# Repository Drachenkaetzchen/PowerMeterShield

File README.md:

#### **Voltage and Current Meter Shield**

This is a shield to measure voltage (±30V) and current (±10A). It is isolated, so you can hook it up either polarity and even measure negative voltages.

#### **Usage Ideas**
- Combine this shield with an SD card shield to create a data-logging multimeter.
- Combine this shield with a WiFi-Shield to log data to the internet.
- Use the WiFi shield with a solar panel to measure how much power you harvest
- Measure the power consumption of your QuadCopter during flight

#### **Theory of Operation**

Voltage is measured using the THS4521 differential amplifier by converting a bipolar single-ended voltage into a differential voltage, which is fed into the ADC.

Current is measured via the 5mΩ shunt resistor and amplified using the INA170 high-side current shunt monitor. It is converted into a voltage and fed into the ADC.  A 1.024V reference is used to level shift the signal for the ADC so that we can measure negative currents as well (negative range: 0-1.024V and positive range 1.024V to 2.048V).

The ADC used is a MCP3426, which supports up to 16 bits of resolution and an integrated gain amplifier (1x, 2x, 4x and 8x), so if you don't need the full input range of ±30V, you can measure smaller voltages with higher resolutions. The ADC is controlled via I²C.

The ADUM1250 isolates the I²C communications and a 5V DC to DC converter isolates the power rails for the shield.

#### **Specifications**
- Voltage Measurements from -30V to +30V
- Current Measurement from -10A to +10A
- Resolution is 12, 14 or 16 bits. This affects the sample rate (Samples per Second or SPS). 15 SPS at 16 Bits, 60 SPS at 14 Bits and 240 SPS at 12 Bits.
- Digital Gain control of 1x, 2x, 4x or 8x gain
- Input Impedance: >10MΩ
- Burden Voltage: 5mV/A
- Resolution for Voltage Measurements at 16 bit: 4mV at 1x gain (±30V), 2mV at 2x gain (±15V), 1mV at 4x gain (±7.5V) and 0.5mV at 8x gain (±3.75V)
- Resolution for Current Measurements at 16 bit: 1.2mA at 1x gain (±10A), 0.6mA at 2x gain (±5A), 0.3mA at 4x gain (±2.5A) and 0.15mA at 8x gain (±1.25A)
- Works out of the box with all Arduino platforms that feature VREF, SDA and SCL pins. For older Arduino platforms, you may wire VREF to +5V and SDA/SCL to A4/A5 pins.

#### **Project History**

I have built a [solar powered router](http://felicitus.org/solarwind/) for which I have designed a voltage and current measurement board. The voltage and current meter shield evolved from that monitoring board.

I have taken great care to make this shield relatively safe; it doesn't matter which way you connect the measurement inputs - your Arduino will survive due to the isolation (unless you exceed the specified ±30V ±10A input ranges).

#### **License**

This board is licensed under the CERN OHL v1.2.

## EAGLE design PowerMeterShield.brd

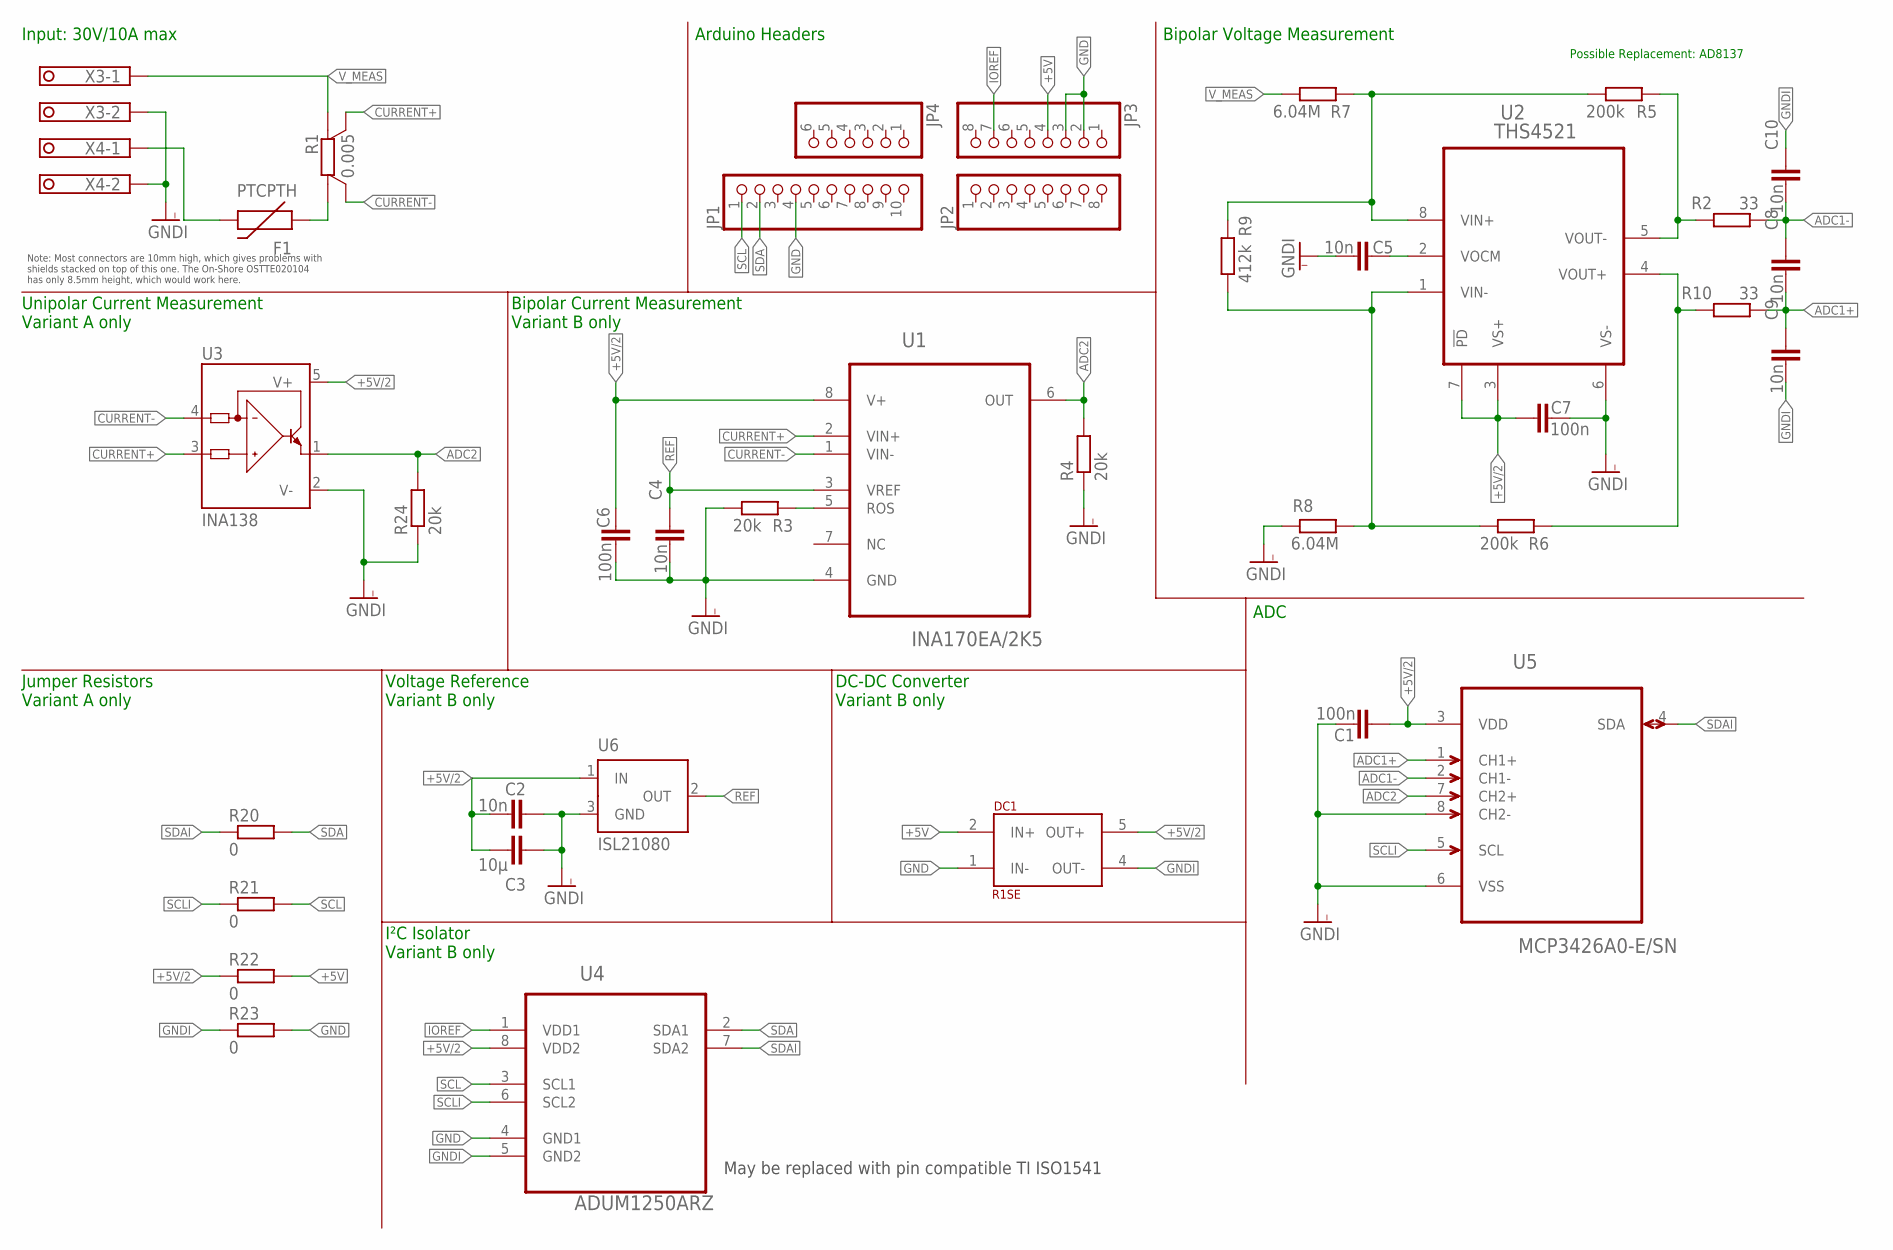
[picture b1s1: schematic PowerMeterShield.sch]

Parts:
C1, C6, C7: 100n; C0805
C2, C4, C5, C8, C9, C10: 10n; C0805
C3: 10µ; C0805
DC1: R1SE
F1: PTCPTH; PTC
JP1: PINHD-1X10; 1X10
JP2, JP3: PINHD-1X8; 1X08
JP4: PINHD-1X6; 1X06
R1: 0.005; CSM3637M
R2, R10: 33; R0805
R3, R4, R24: 20k; R0805
R5, R6: 200k; R0805
R7, R8: 6.04M; R0805
R9: 412k; R0805
R20, R21, R22, R23: 0; R2010
U1: INA170EA/2K5; SOP65P490X110-8N
U2: THS4521; SOIC127P600X175-8N
U3: INA138; SOT23-5
U4: ADUM1250ARZ; SOIC127P600X175-8N
U5: MCP3426A0-E/SN; SOIC127P600X175-8N
U6: ISL21080; SOT23
X3, X4: 1751248

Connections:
+5V: DC1.2 (IN+), JP3.4, R22.2
+5V/2: C1.1, C2.1, C3.1, C6.1, C7.1, DC1.5 (OUT+), R22.1, U1.8 (V+), U2.3 (VS+), U2.7 (!PD), U3.5 (V+), U4.8 (VDD2), U5.3 (VDD), U6.1 (IN)
ADC1+: C8.1, C9.2, R10.1, U5.1 (CH1+)
ADC1+_OLD: R6.2, R10.2, U2.4 (VOUT+)
ADC1-: C8.2, C10.1, R2.1, U5.2 (CH1-)
ADC1-_OLD: R2.2, R5.2, U2.5 (VOUT-)
ADC2: R4.2, R24.2, U1.6 (OUT), U3.1 (OUT), U5.7 (CH2+)
CURRENT+: R1.S2, U1.2 (VIN+), U3.3 (IN+)
CURRENT-: R1.S1, U1.1 (VIN-), U3.4 (IN-)
GND: DC1.1 (IN-), JP1.4, JP3.2, JP3.3, R23.2, U4.4 (GND1)
GNDI: C1.2, C2.2, C3.2, C4.1, C5.1, C6.2, C7.2, C9.1, C10.2, DC1.4 (OUT-), R3.1, R4.1, R8.1, R23.1, R24.1, U1.4 (GND), U2.6 (VS-), U3.2 (V-), U4.5 (GND2), U5.6 (VSS), U5.8 (CH2-), U6.3 (GND), X3.2, X4.2
IOREF: JP3.7, U4.1 (VDD1)
unnamed: C5.2, U2.2 (VOCM)
unnamed: R5.1, R7.2, R9.2, U2.8 (VIN+)
unnamed: F1.P$1 (1), R1.I1
unnamed: R3.2, U1.5 (ROS)
unnamed: R6.1, R8.2, R9.1, U2.1 (VIN-)
REF: C4.2, U1.3 (VREF), U6.2 (OUT)
SCL: JP1.1, R21.2, U4.3 (SCL1)
SCLI: R21.1, U4.6 (SCL2), U5.5 (SCL)
SDA: JP1.2, R20.2, U4.2 (SDA1)
SDAI: R20.1, U4.7 (SDA2), U5.4 (SDA)
VIN_MEAS: F1.P$2 (2), X4.1
V_MEAS: R1.I2, R7.1, X3.1

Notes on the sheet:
Input: 30V/10A max
Voltage Reference Variant B only
DC-DC Converter Variant B only
Arduino Headers
ADC
I²C Isolator Variant B only
Bipolar Voltage Measurement
Bipolar Current Measurement Variant B only
Unipolar Current Measurement Variant A only
Jumper Resistors Variant A only
Note: Most connectors are 10mm high, which gives problems with shields stacked on top of this one. The On-Shore OSTTE020104 has only 8.5mm height, which would work here.
May be replaced with pin compatible TI ISO1541
Possible Replacement: AD8137

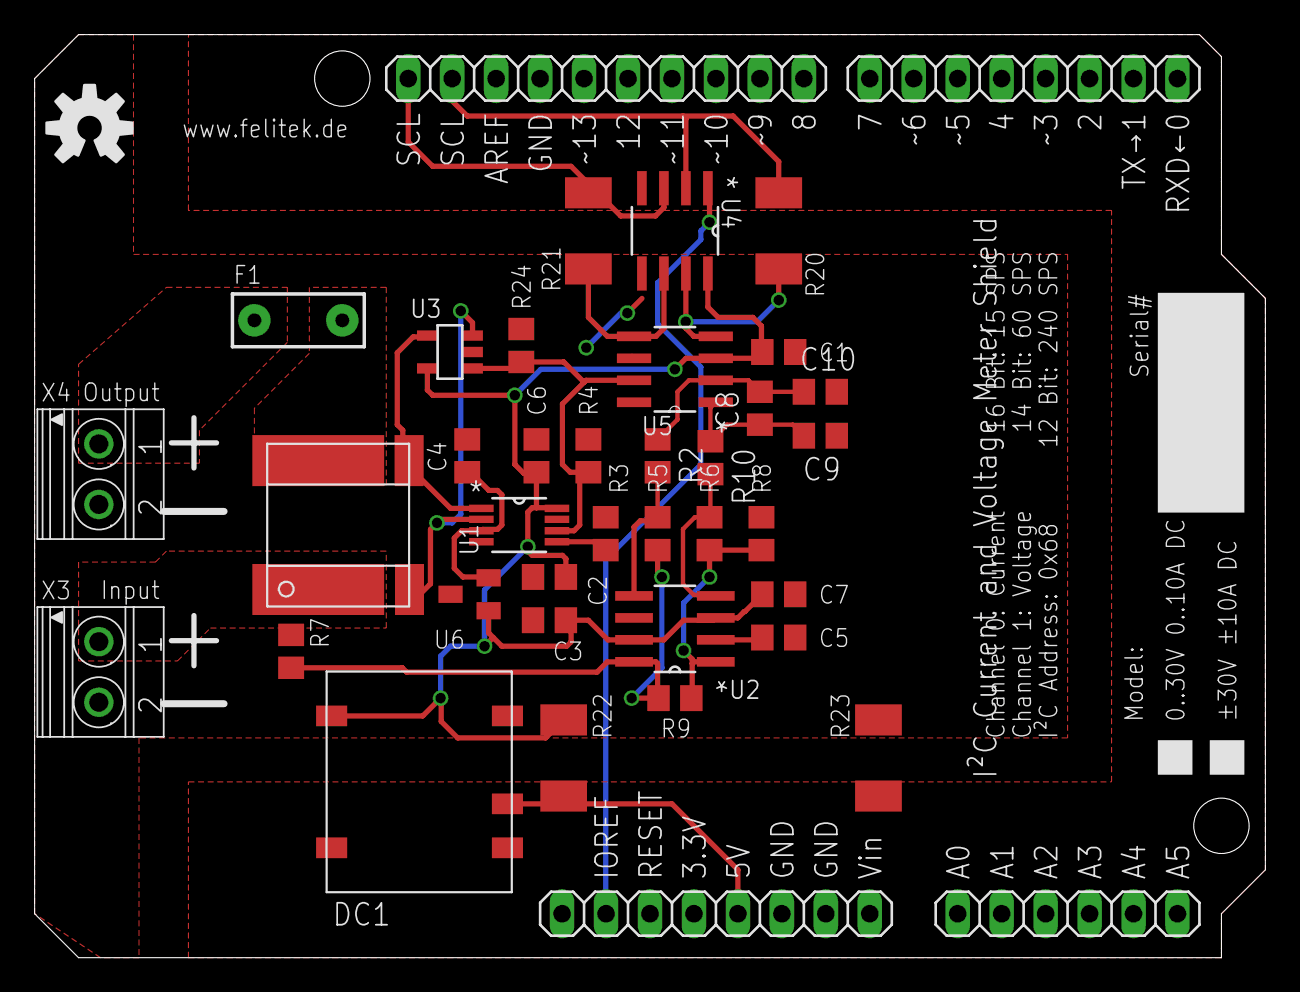
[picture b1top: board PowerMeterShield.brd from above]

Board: 2 copper layers, 71.1 x 53.3 mm, 40 parts (0 on the bottom side), 24 nets.

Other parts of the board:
U$1: OSHW-LOGO-M

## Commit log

2013-08-20 Added DC-DC converter to isolate circuit; still missing optocouplers and differential voltage measurement
2013-08-21 Added I²C isolation
2013-08-21 Added creepage distance of about 3mm for a bit of safety™
2013-08-22 Finalized design, made PCB larger in order to compensate for heigher components than the headers, so users can stack other shields on top of ours (hopefully).
2013-08-29 Added readme, added TME for the ADUM1250 isolator
2013-08-30 Added port names to silkscreen, added I²C pullups for the internal I²C bus
2013-08-30 Added use cases to the README, added mains warning
2014-01-23 Updated to a modified design for differential voltage measurement
2014-01-23 Added domain name + descriptions for the functional schematic blocks
2014-01-23 Added functional block descriptions + url on board
2014-01-25 Aded cern ohl 1.2 license
2014-01-29 Added non-isolated variant
2014-01-29 Moved logo and website a bit towards the top to align nicely with the isolation
2014-01-29 More fine-adjustments to be symmetric with the isolation planes
2014-01-29 Added device address to silkscreen
2014-01-29 Fixed trace width, added polyfuse
2014-01-29 Removed obsolete GND via
2014-01-29 Fixed fuse designator, misc silkscreen fixes
2014-01-29 In/Out Sockets conflict with some Arduino's USB/Power jacks, added keepout regions and moved the jacks Reworked the traces from the inputs/outputs to be polygons, thanks moemoe!
2014-01-29 Made "Isolate" for the trace-replacement polygons higher
2014-01-29 Added SMD DC-DC converter to match height of the shield headers (old one was 10mm high, new one is only 6.3mm high) Added silkscreen for the arduino headers
2014-01-29 Removed double A5 silkscreen Fixed size for the + signs
2014-01-29 Adjusted R20-R23 positions
2014-01-29 Fixed DC-DC converter footprint
2014-01-29 Configured minimum clearance of 15mil for the inputs
2014-01-29 Added prices + order codes
2014-02-07 Added experimental serial line resistors and capacitors

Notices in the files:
parts and their libraries:
SparkFun: Licensing: CC v3.0 Share-Alike You are welcome to use this library for commercial purposes.
